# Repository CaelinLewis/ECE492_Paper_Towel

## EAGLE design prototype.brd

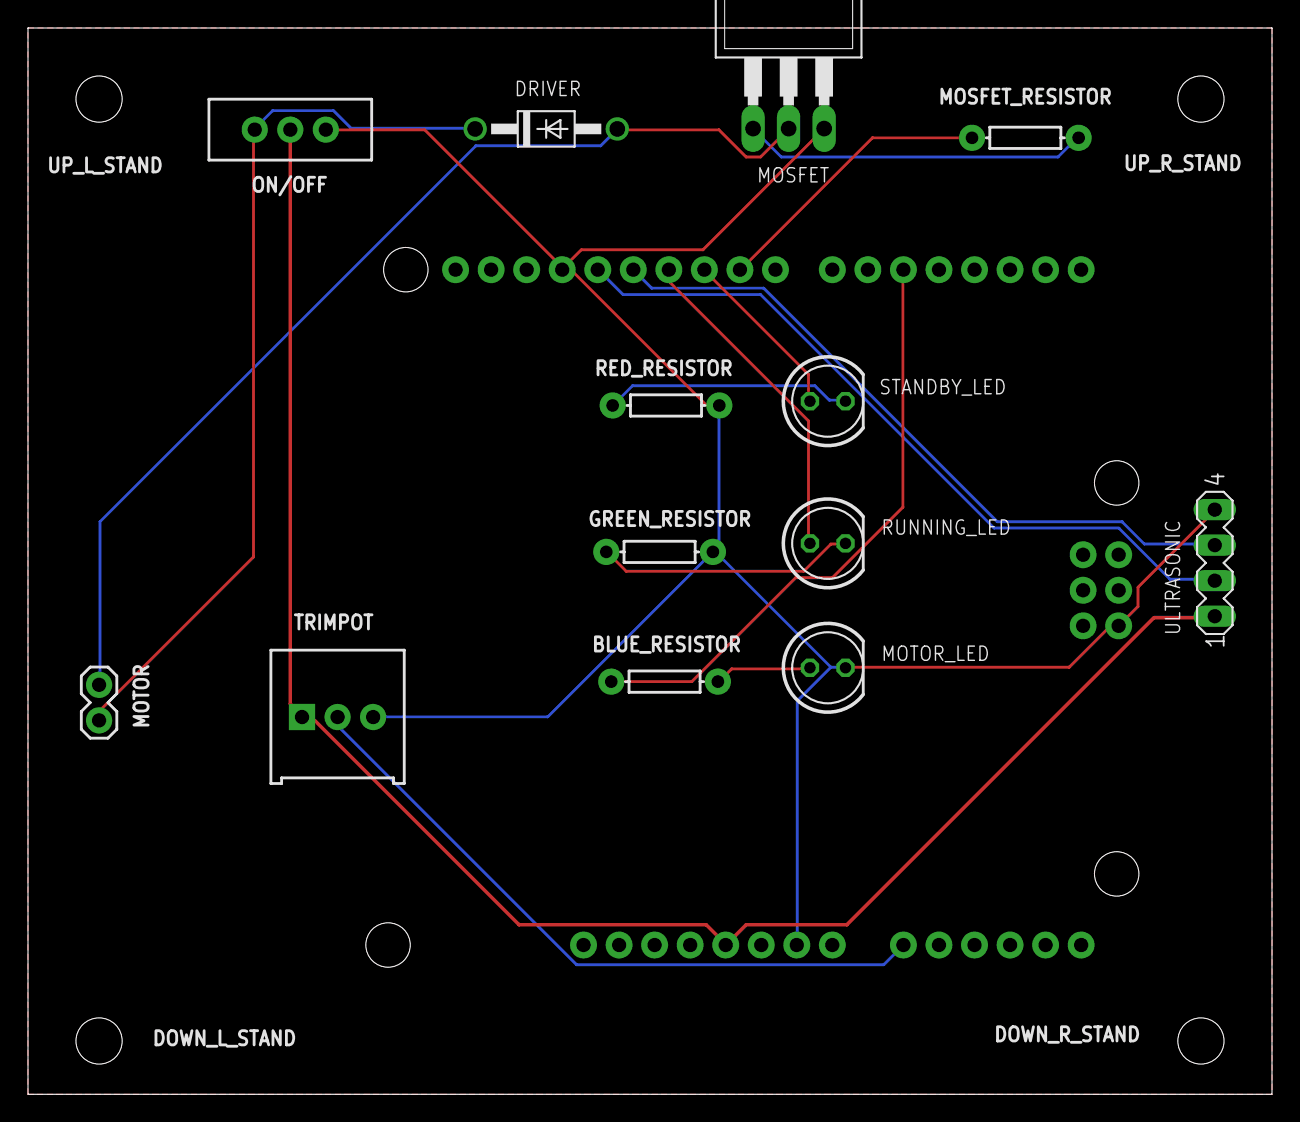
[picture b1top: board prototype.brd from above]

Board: 2 copper layers, 88.9 x 76.2 mm, 18 parts (0 on the bottom side), 15 nets.

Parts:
B1: ARDUINO_UNO_R3; ARDUINO_R3
BLUE_RESISTOR: 330; AXIAL-0.3
DOWN_L_STAND: STAND-OFF
DOWN_R_STAND: STAND-OFF
DRIVER: 1N4004; DO41-10
GREEN_RESISTOR: 330; AXIAL-0.3
MOSFET: IRFZ48Z; TO220BH
MOSFET_RESISTOR: 1k; AXIAL-0.3
MOTOR: 1X02
MOTOR_LED: BLUE; LED5MM
ON/OFF: SWITCH_SPDT_PTH_11.6X4.0MM
RED_RESISTOR: 330; AXIAL-0.3
RUNNING_LED: GREEN; LED5MM
STANDBY_LED: RED; LED5MM
TRIMPOT: 10k; TRIMPOT-PTH-3386U
ULTRASONIC: MA04-1
UP_L_STAND: STAND-OFF
UP_R_STAND: STAND-OFF

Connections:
BLUE: B1.D5, BLUE_RESISTOR.P$1
ECHO: B1.D12, ULTRASONIC.3
GND: B1.GND@2, B1.GND@3, B1.GND@4, GREEN_RESISTOR.P$2, MOSFET.S, MOTOR_LED.K, ON/OFF.3, RED_RESISTOR.P$2, TRIMPOT.3, ULTRASONIC.4
GREEN: B1.D11, RUNNING_LED.A
MOSFET: B1.D9, MOSFET_RESISTOR.P$1
unnamed: DRIVER.C, MOTOR.1, ON/OFF.1
unnamed: RED_RESISTOR.P$1, STANDBY_LED.K
unnamed: GREEN_RESISTOR.P$1, RUNNING_LED.K
unnamed: MOSFET.G, MOSFET_RESISTOR.P$2
unnamed: BLUE_RESISTOR.P$2, MOTOR_LED.A
unnamed: DRIVER.A, MOSFET.D, MOTOR.2
POTENTIOMETER: B1.A0, TRIMPOT.2
RED: B1.D10, STANDBY_LED.A
TRIG: B1.D13, ULTRASONIC.2
VCC: B1.5V, ON/OFF.2, TRIMPOT.1, ULTRASONIC.1

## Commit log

2018-06-20 Added the schematic and the board
2018-06-23 Final Draft of board
2018-06-23 Final Draft of schematic

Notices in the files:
parts and their libraries:
SparkFun-Boards: Licensing: Creative Commons ShareAlike 4.0 International - https://creativecommons.org/licenses/by-sa/4.0
